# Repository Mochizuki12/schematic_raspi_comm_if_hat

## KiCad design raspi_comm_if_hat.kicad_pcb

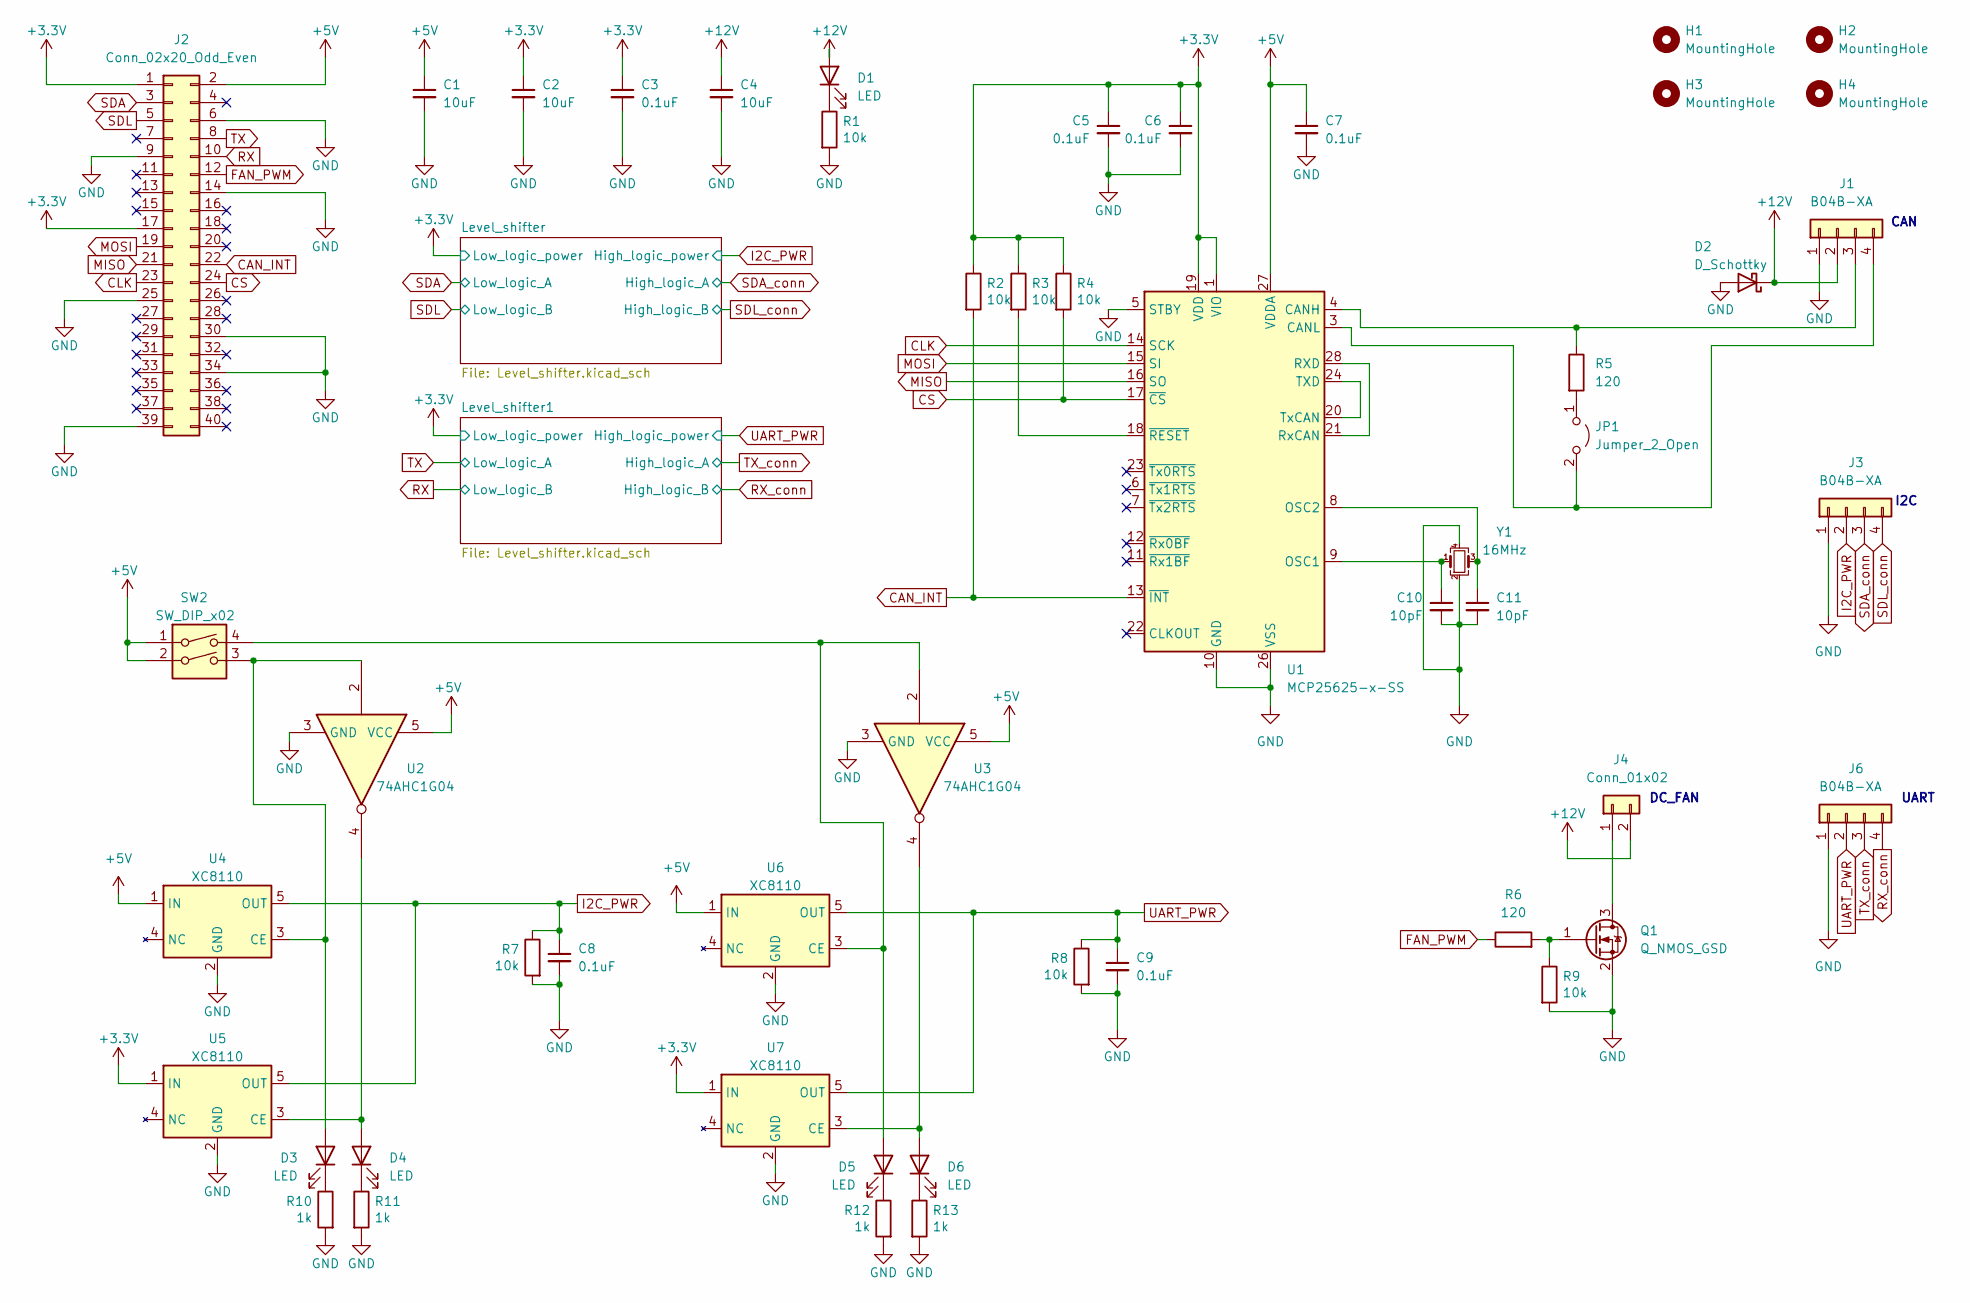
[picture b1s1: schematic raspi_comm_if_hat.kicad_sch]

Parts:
C1, C2, C4: 10uF; C_0603_1608Metric; LCSC C96446
C3, C5, C6, C7, C8, C9: 0.1uF; C_0402_1005Metric; LCSC C307331
C10, C11: 10pF; C_0402_1005Metric; LCSC C32949
D1, D3, D4, D5, D6: LED; LED_0603_1608Metric; LCSC C2286
D2: D_Schottky; D_SOD-123F; LCSC C7502712
H1, H2, H3, H4: MountingHole; MountingHole_2.7mm_M2.5
J1, J3, J6: B04B-XA; JST_XA_S04B-XASK-1_1x04_P2.50mm_Horizontal
J2: Conn_02x20_Odd_Even; PinSocket_2x20_P2.54mm_Vertical
J4: Conn_01x02; JST_XA_B02B-XASK-1_1x02_P2.50mm_Vertical
JP1: Jumper_2_Open; PinHeader_1x02_P2.54mm_Vertical
Q1: Q_NMOS_GSD; SOT-23; LCSC C20917
R1, R2, R3, R4, R7, R8, R9: 10k; R_0402_1005Metric; LCSC C25744
R5: 120; R_0603_1608Metric; LCSC C22787
R6: 120; R_0402_1005Metric; LCSC C25079
R10, R11, R12, R13: 1k; R_0402_1005Metric; LCSC C11702
SW2: SW_DIP_x02; SW_DIP_SPSTx02_Slide_Copal_CHS-02B_W7.62mm_P1.27mm
U1: MCP25625-x-SS; SSOP-28_5.3x10.2mm_P0.65mm; LCSC C184944
U2, U3: 74AHC1G04; SOT-23-5; LCSC C460486
U4, U5, U6, U7: XC8110; SOT-23-5; LCSC C3235547
Y1: 16MHz; Crystal_SMD_3225-4Pin_3.2x2.5mm; LCSC C13738

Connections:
+3.3V: C2.1, C3.1, C5.1, C6.1, J2.1, J2.17, R2.1, R3.1, R4.1, U1.1 (VIO), U1.19 (VDD), U5.1 (IN), U7.1 (IN); also elsewhere on the board
+5V: C1.1, C7.1, J2.2, SW2.1, SW2.2, U1.27 (VDDA), U2.5 (VCC), U3.5 (VCC), U4.1 (IN), U6.1 (IN)
+12V: C4.1, D1.2 (A), D2.1 (K), J1.2, J4.2
CAN_INT: J2.22, R2.2, U1.13 (~INT)
CLK: J2.23, U1.14 (SCK)
CS: J2.24, R4.2, U1.17 (~CS)
FAN_PWM: J2.12, R6.1
GND: C1.2, C2.2, C3.2, C4.2, C5.2, C6.2, C7.2, C8.2, C9.2, C10.2, C11.2, D2.2 (A), J1.1, J2.6, J2.9, J2.14, J2.25, J2.30, J2.34, J2.39, J3.1, J6.1, Q1.2 (S), R1.2, R7.2, R8.2, R9.2, R10.2, R11.2, R12.2, R13.2, U1.5 (STBY), U1.10 (GND), U1.26 (VSS), U2.3 (GND), U3.3 (GND), U4.2 (GND), U5.2 (GND), U6.2 (GND), U7.2 (GND), Y1.2, Y1.4
I2C_PWR: C8.1, J3.2, R7.1, U4.5 (OUT), U5.5 (OUT); also elsewhere on the board
MISO: J2.21, U1.16 (SO)
MOSI: J2.19, U1.15 (SI)
unnamed: D1.1 (K), R1.1
unnamed: D3.2 (A), SW2.3, U2.2, U4.3 (CE)
unnamed: D3.1 (K), R10.1
unnamed: D4.2 (A), U2.4, U5.3 (CE)
unnamed: D4.1 (K), R11.1
unnamed: D5.2 (A), SW2.4, U3.2, U6.3 (CE)
unnamed: D5.1 (K), R12.1
unnamed: D6.2 (A), U3.4, U7.3 (CE)
unnamed: D6.1 (K), R13.1
unnamed: J1.3, R5.1, U1.4 (CANH)
unnamed: J1.4, JP1.2 (B), U1.3 (CANL)
unnamed: J4.1, Q1.3 (D)
unnamed: JP1.1 (A), R5.2
unnamed: Q1.1 (G), R6.2, R9.1
unnamed: C10.1, U1.9 (OSC1), Y1.1
unnamed: C11.1, U1.8 (OSC2), Y1.3
unnamed: U1.21 (RxCAN), U1.28 (RXD)
unnamed: U1.20 (TxCAN), U1.24 (TXD)
unnamed: R3.2, U1.18 (~RESET)
RX: J2.10; also elsewhere on the board
RX_conn: J6.4; also elsewhere on the board
SDA: J2.3; also elsewhere on the board
SDA_conn: J3.3; also elsewhere on the board
SDL: J2.5; also elsewhere on the board
SDL_conn: J3.4; also elsewhere on the board
TX: J2.8; also elsewhere on the board
TX_conn: J6.3; also elsewhere on the board
UART_PWR: C9.1, J6.2, R8.1, U6.5 (OUT), U7.5 (OUT); also elsewhere on the board

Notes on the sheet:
DC_FAN
CAN
I2C
UART

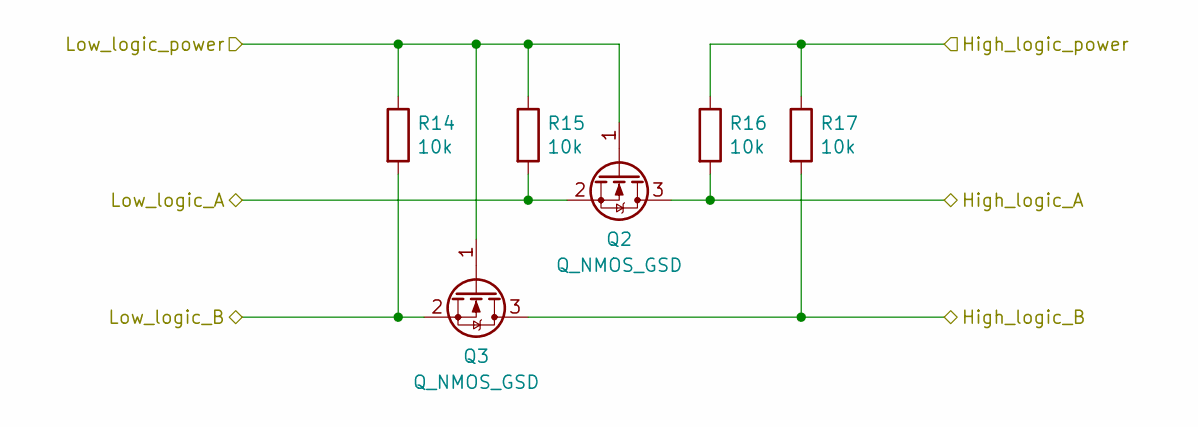
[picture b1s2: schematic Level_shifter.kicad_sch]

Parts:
Q2, Q3: Q_NMOS_GSD; SOT-23; LCSC C7420339
R14, R15, R16, R17: 10k; R_0402_1005Metric; LCSC C25744

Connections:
+3.3V: Q2.1 (G), Q3.1 (G), R14.1, R15.1; also elsewhere on the board
I2C_PWR: R16.1, R17.1; also elsewhere on the board
SDA: Q2.2 (S), R15.2; also elsewhere on the board
SDA_conn: Q2.3 (D), R16.2; also elsewhere on the board
SDL: Q3.2 (S), R14.2; also elsewhere on the board
SDL_conn: Q3.3 (D), R17.2; also elsewhere on the board

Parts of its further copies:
Q4, Q5: Q_NMOS_GSD; SOT-23; LCSC C7420339
R18, R19, R20, R21: 10k; R_0402_1005Metric; LCSC C25744

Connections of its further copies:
+3.3V: Q4.1 (G), Q5.1 (G), R18.1, R19.1; also elsewhere on the board
RX: Q5.2 (S), R18.2; also elsewhere on the board
RX_conn: Q5.3 (D), R21.2; also elsewhere on the board
TX: Q4.2 (S), R19.2; also elsewhere on the board
TX_conn: Q4.3 (D), R20.2; also elsewhere on the board
UART_PWR: R20.1, R21.1; also elsewhere on the board

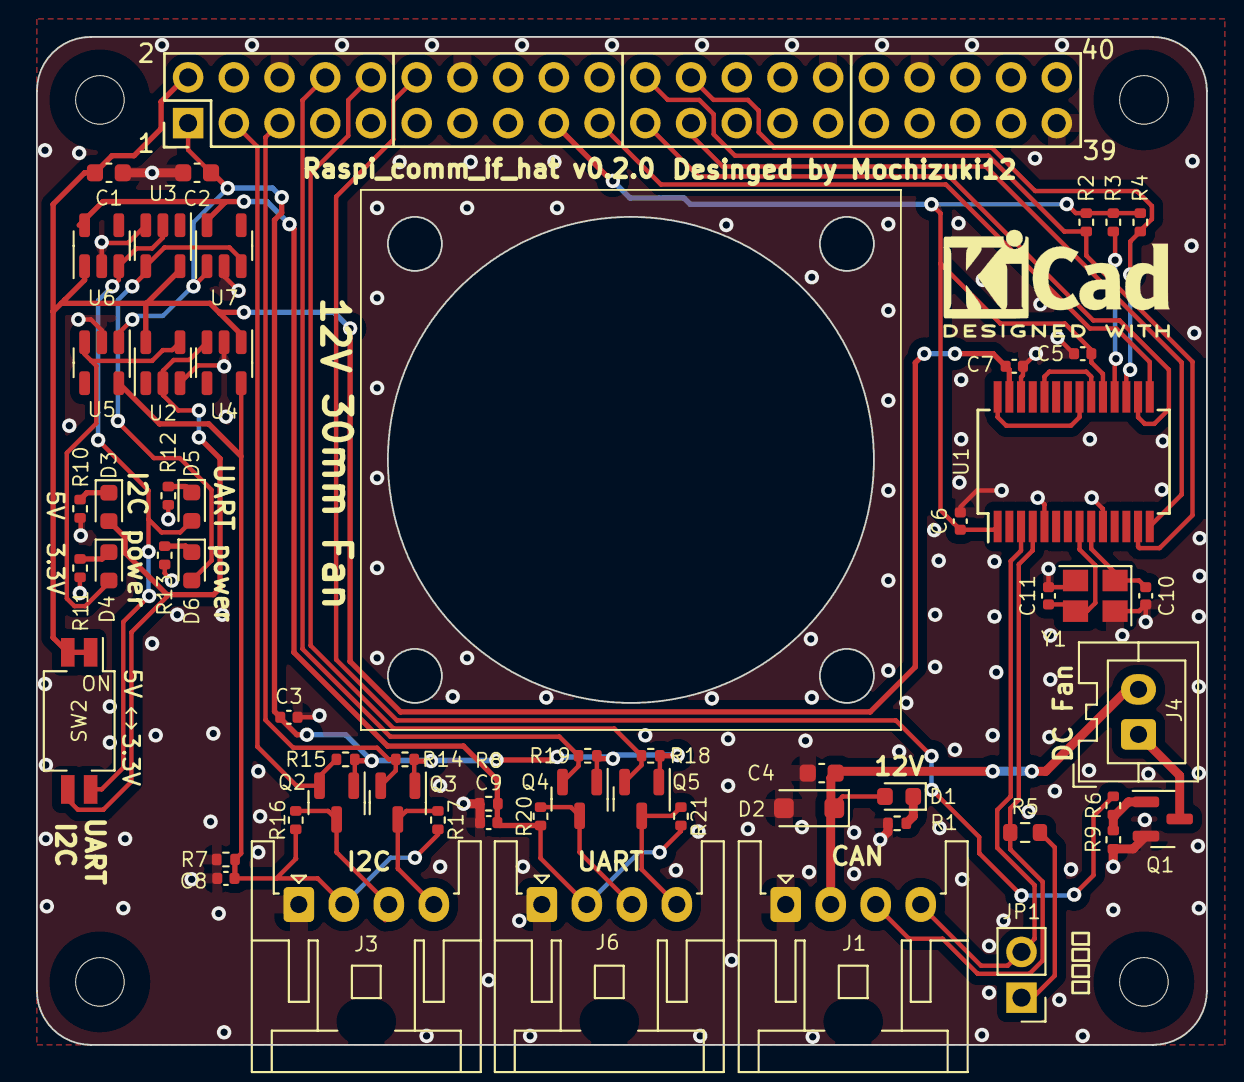
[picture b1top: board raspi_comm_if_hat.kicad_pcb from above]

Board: 2 copper layers, 65.0 x 56.0 mm, 62 parts (1 on the bottom side), 39 nets.

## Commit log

2024-11-27 draw schemtic & PCB
2024-11-28 update pcb
2024-11-30 add fan connector
2024-12-10 v0.1.0
2025-05-09 Update of data for PCBA
2025-05-09 Add LSCS
2025-05-11 v0.2.0 release
